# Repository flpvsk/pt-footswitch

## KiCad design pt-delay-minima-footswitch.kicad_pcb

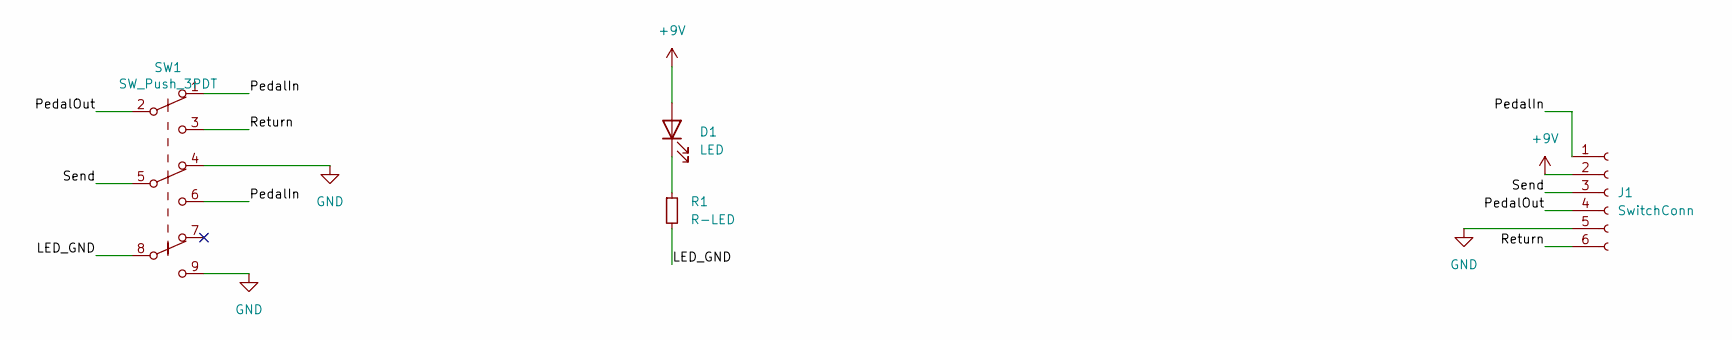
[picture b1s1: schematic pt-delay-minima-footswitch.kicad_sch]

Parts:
D1: LED; LED_Rectangular_W5.0mm_H2.0mm
J1: SwitchConn; PinHeader_1x06_P2.54mm_Vertical
R1: R-LED; R_Axial_DIN0207_L6.3mm_D2.5mm_P7.62mm_Horizontal
SW1: SW_Push_3PDT; 3PDT.LUGS.FLPVSK

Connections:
+9V: D1.2 (A), J1.2
/LED_GND: R1.2, SW1.8 (B)
/PedalIn: J1.1, SW1.1 (A), SW1.6 (C)
/PedalOut: J1.4, SW1.2 (B)
/Return: J1.6, SW1.3 (C)
/Send: J1.3, SW1.5 (B)
GND: J1.5, SW1.4 (A), SW1.9 (C)
unnamed: D1.1 (K), R1.1

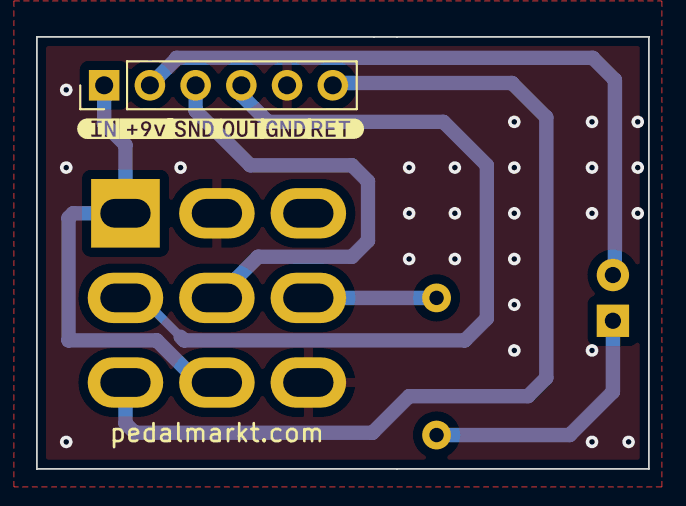
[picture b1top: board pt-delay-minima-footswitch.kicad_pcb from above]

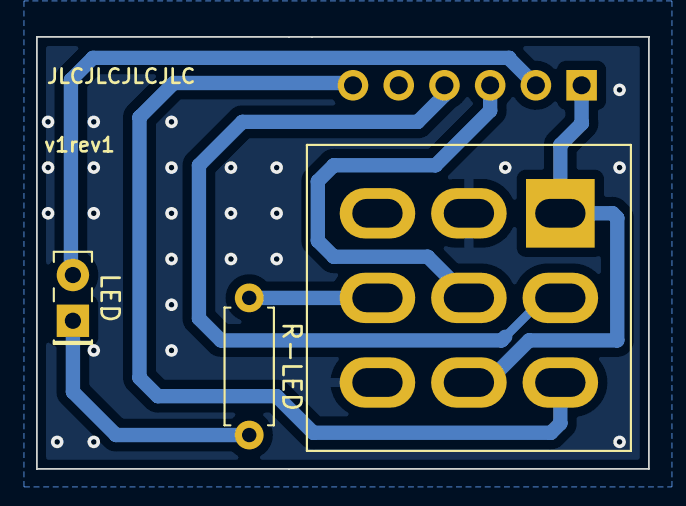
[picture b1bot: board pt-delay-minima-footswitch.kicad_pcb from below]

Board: 2 copper layers, 34.0 x 24.0 mm, 10 parts (2 on the bottom side), 8 nets.

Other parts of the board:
kibuzzard-65BA2AF1: G***; kibuzzard-65BA2AF1
kibuzzard-65F1D5BE: G***; kibuzzard-65F1D5BE
kibuzzard-65F1D5F5: G***; kibuzzard-65F1D5F5
kibuzzard-65F1D58A: G***; kibuzzard-65F1D58A
kibuzzard-65F1D61D: G***; kibuzzard-65F1D61D
kibuzzard-65F1D635: G***; kibuzzard-65F1D635

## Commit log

2024-03-23 v1rev1
2024-03-23 Added versions
